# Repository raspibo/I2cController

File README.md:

# I2cController
Evolution of I2C_rotary_encoder, a board with lcd, rotary encoder, push buttons for general purpose input/output over I2C bus

Whit this board you can interact with a standard hardware equipment of rotary encoder, lcd display, push buttons over I2C, you can 
also mount a partial set of peripherals.

The code handle interrupt of pin change generated from MC23017 chip when event fire on buttons or rotary encoder.

# Use
Put portable dir under your arduino folder to use project specific libraries

# Typical Schematic

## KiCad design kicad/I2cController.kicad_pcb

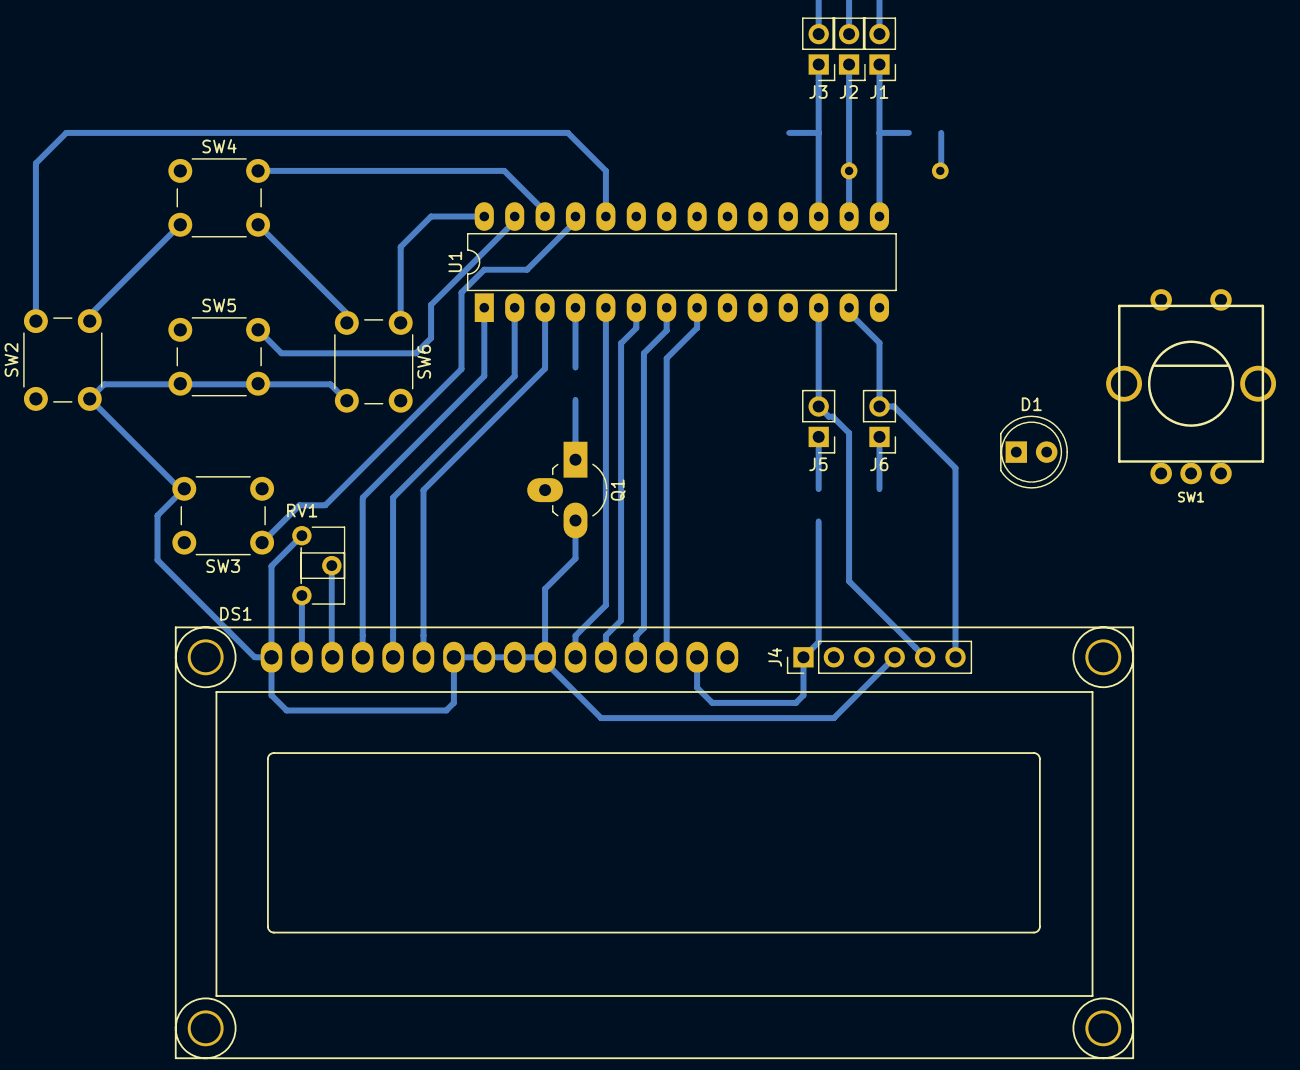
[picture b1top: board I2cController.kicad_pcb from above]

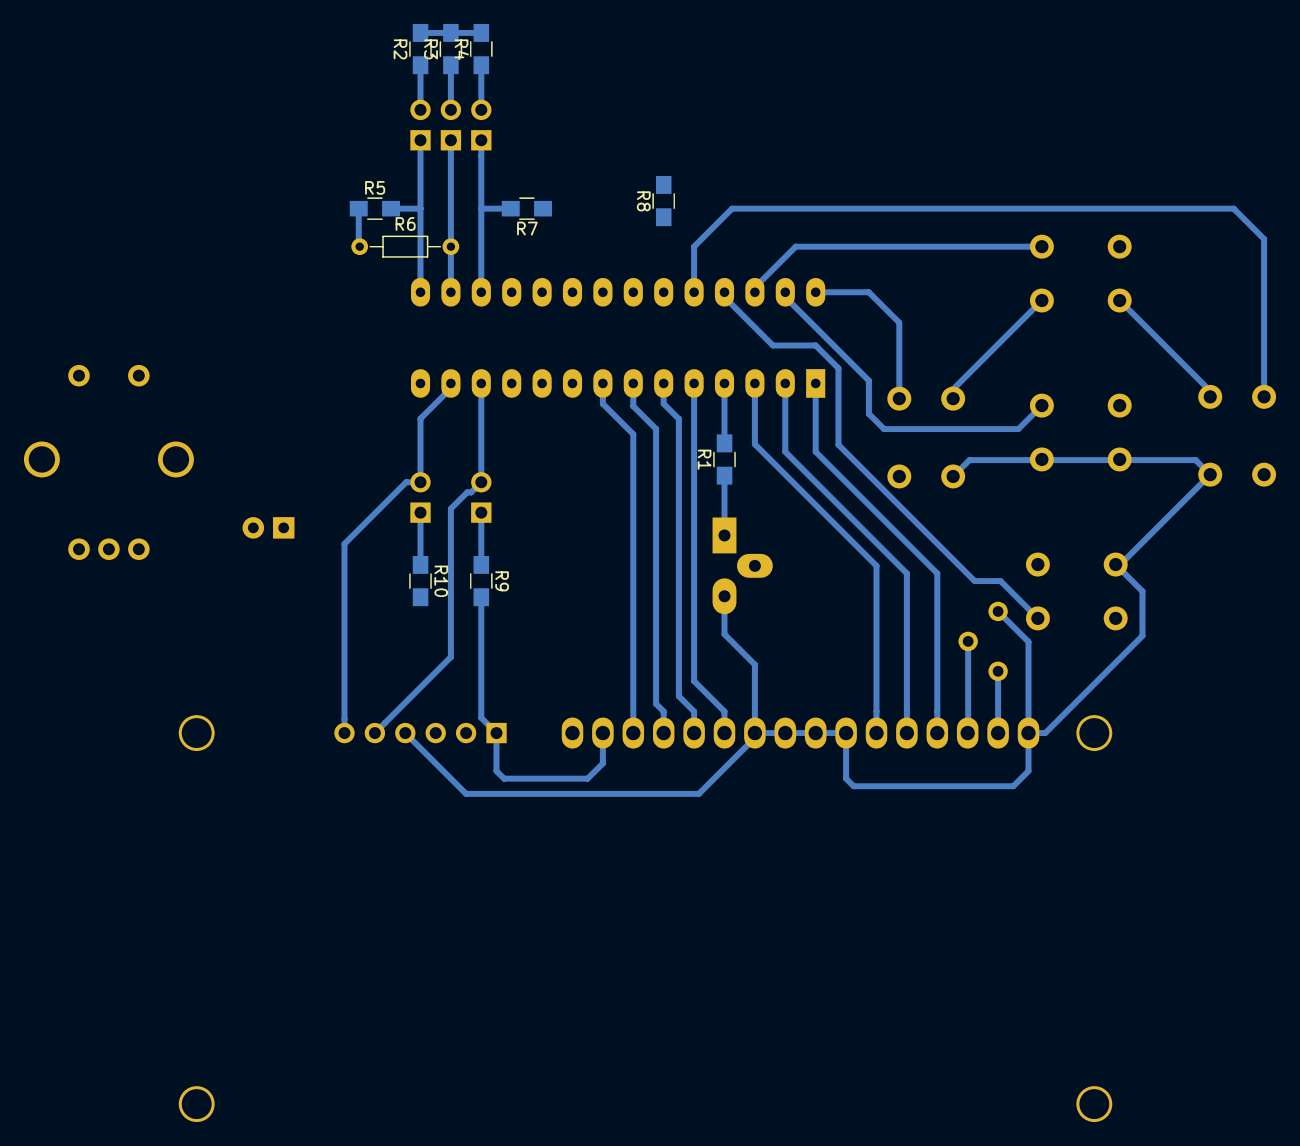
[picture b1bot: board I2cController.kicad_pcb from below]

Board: 2 copper layers, 27 parts (10 on the bottom side), 34 nets.

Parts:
D1: LED; LED_D5.0mm
DS1: LCD16X2; WC1602A
J1, J2, J3, J5, J6: CONN_02X01; Pin_Header_Straight_1x02_Pitch2.54mm
J4: CONN_01X06; Pin_Header_Straight_1x06_Pitch2.54mm
Q1: Q_NPN_BCE; TO-92_Rugged_Reverse
R1, R2, R3, R4, R5, R7, R8, R9, R10: R; R_0805_HandSoldering
R6: R; R_Axial_DIN0204_L3.6mm_D1.6mm_P7.62mm_Horizontal
RV1: POT; Potentiometer_Trimmer_ACP_CA6h_Vertical
SW1: Rotary_Encoder_Switch; SF-ROTARY-ENCODER
SW2, SW3, SW4, SW5, SW6: SW_Push; SW_PUSH_6mm_h7.3mm
U1: MCP23017; DIP-28_W7.62mm_LongPads

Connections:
GND: DS1.1, DS1.7, DS1.8, DS1.9, DS1.10, J4.4, Q1.3, R5.1, R6.1, R7.1, RV1.1, SW1.2, SW1.5, SW2.2, SW3.2, SW4.2, SW5.2, SW6.2, U1.10
L_D0: DS1.4, U1.1
L_D1: DS1.5, U1.2
L_D2: DS1.6, U1.3
L_D3: R1.2, U1.4
L_D4: DS1.11, U1.5
L_D5: DS1.12, U1.6
L_D6: DS1.13, U1.7
L_D7: DS1.14, U1.8
unnamed: D1.1, R8.1
unnamed: DS1.3, RV1.2
unnamed: DS1.16, Q1.2
unnamed: J1.1, R5.2, U1.15
unnamed: J1.2, R2.1
unnamed: J2.1, R6.2, U1.16
unnamed: J2.2, R3.1
unnamed: J3.1, R7.2, U1.17
unnamed: J3.2, R4.1
unnamed: J4.2, U1.18
unnamed: J4.3, R8.2, U1.20
unnamed: J5.1, R9.1
unnamed: J6.1, R10.1
unnamed: Q1.1, R1.1
unnamed: SW1.1, U1.22
unnamed: SW1.3, U1.21
unnamed: SW1.4, U1.23
unnamed: SW2.1, U1.24
unnamed: SW3.1, U1.25
unnamed: SW4.1, U1.26
unnamed: SW5.1, U1.27
unnamed: SW6.1, U1.28
SCL: J4.5, J5.2, U1.12
SDA: J4.6, J6.2, U1.13
VCC: D1.2, DS1.2, DS1.15, J4.1, R2.2, R3.2, R4.2, R9.2, R10.2, RV1.3, U1.9

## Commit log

2017-04-13 Create README.md
    First commit, project description
2017-04-13 first code commit only few functions
2017-04-20 Library fusion between LiquiTWI2 and Adafruit MCP23017
2017-04-20 Add kicad schematic
2017-04-20 remove old schematic
2017-04-21 OK encoder sequence
2017-04-22 Encoder OK, buttons OK
2017-04-22 Cross config function OK
2017-04-22 remove files from archive
2017-04-22 update gitignore
2017-04-23 unwanted file
2017-04-23 Remove lib
2017-04-23 Add lib and archive cleaning
2017-04-23 Update reference of code
